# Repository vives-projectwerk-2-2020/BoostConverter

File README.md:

# BoostConverter

## Description

This project is under the MIT license, view it here [MIT license](license.md)
The solar charge board can only deliver 3V3 so we had to make a board that's convert the 3V3 to 5V. We need to do this because the SDS011 sensor has to work on 5V.

## Schematic of the boost converter

In this schematic you can see one big central component the MCP1640CT-I/MC. This component is a synchronous boost regulator with true output disconnect or input/output bypass option. This boost regulator is a DC-DC converter. There are also pins (SV1) provided to connect this board to the sensor board. On the schematic you can also see a coil we needed to put this in the schematic otherwise it was not possible to get the 3V3 to 5 V. There are also other components like resistors and capacitors.

## Board schematic of the boost converter

## Pin layout boost regulator

Here you can see the pin layout of the MCP1640CT-I/MC synchronous boost regulator.

## Partlist boost converter

* [4.7 µF capacitor](https://be.farnell.com/taiyo-yuden/lmk107bj475ka-t/cap-4-7-f-10v-10-x5r-0603/dp/2112745?ost=2112745&ddkey=https%3Anl-BE%2FElement14_Belgium%2Fsearch)
* [10 µF capacitor](https://be.farnell.com/murata/grm188c81c106ma73d/cap-10-f-16v-20-x6s-0603/dp/2470486?ost=2470486&ddkey=https%3Anl-BE%2FElement14_Belgium%2Fsearch)
* [4.7 µH power inductor](https://be.farnell.com/coilcraft/lps4018-472mrb/inductor-4-7uh-20-1-3a-shld-smd/dp/2408103?st=4.7%20%C2%B5H%20inductor)
* [976 kohm resistor](https://be.farnell.com/multicomp/mcwr06x9763ftl/res-976k-1-0-1w-0603-thick-film/dp/2694973?ost=2694973&ddkey=https%3Anl-BE%2FElement14_Belgium%2Fsearch)
* [309 kohm resistor](https://be.farnell.com/vishay/crcw0603309kfkea/res-309k-1-0-1w-0603-thick-film/dp/2138544?st=2138544)
* [4 male pins](https://be.farnell.com/amp-te-connectivity/826629-4/header-1row-4way/dp/3418303?ost=3418303&ddkey=https%3Anl-BE%2FElement14_Belgium%2Fsearch)
* [Boost regulator](https://www.digikey.be/products/nl?keywords=MCP1640CT-I%2FMCCT-ND)

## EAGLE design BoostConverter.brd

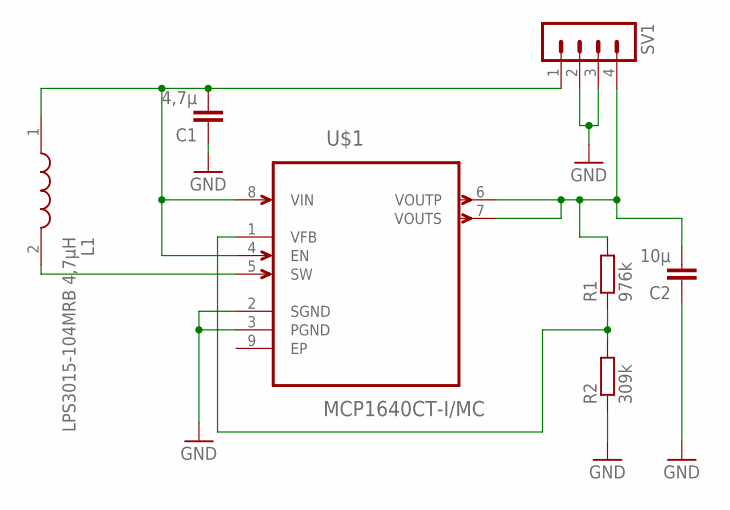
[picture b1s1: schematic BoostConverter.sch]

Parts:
C1: 4,7µ; C0603
C2: 10µ; C0603
L1: LPS3015-104MRB 4,7µH; LPS3015
R1: 976k; R0603
R2: 309k; R0603
SV1: MA04-1
U$1: MCP1640CT-I/MC; DFN200X300X100-9N

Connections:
GND: C1.1, C2.1, R2.1, SV1.2, SV1.3, U$1.2 (SGND), U$1.3 (PGND)
unnamed: C1.2, L1.1, SV1.1, U$1.4 (EN), U$1.8 (VIN)
unnamed: L1.2, U$1.5 (SW)
unnamed: C2.2, R1.2, SV1.4, U$1.6 (VOUTP), U$1.7 (VOUTS)
unnamed: R1.1, R2.2, U$1.1 (VFB)

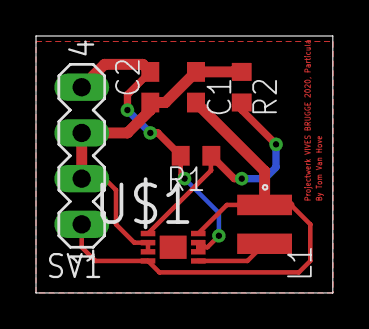
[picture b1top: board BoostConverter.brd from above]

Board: 2 copper layers, 16.5 x 14.3 mm, 7 parts (0 on the bottom side), 5 nets.

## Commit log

2020-05-14 adding the schematic and board
2020-05-14 adding the partlist & finishing the project
2020-05-21 added pictures of the boost converter the shematic and the board
2020-05-21 added pin layour boost regulator
2020-05-21 added partlist
2020-05-22 adding the license file and include a link to it in the readme
